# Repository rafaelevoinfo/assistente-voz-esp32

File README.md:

# Assistente de voz "Hi ESP"

Assistente de voz caseiro: você diz **"Hi ESP"** perto de uma placa ESP32-S3, conversa por voz com o **Gemini Live** e, quando o pedido é de programação, ele é **delegado ao Claude Code**. A resposta do Claude Code é falada sozinha quando a tarefa termina, mesmo minutos depois.

```
Mesa                                    VPS (Docker / Dokploy)
┌───────────────────────────┐           ┌────────────────────────────────────────────┐
│ INMP441 ─I2S─► ESP32-S3    │  Wi-Fi    │ servidor (Python + Pipecat)                 │
│   • wake word "Hi ESP"     │◄════════► │   • conversa ◄══► Gemini Live               │
│   • WebSocket              │  WSS      │   • pedidos de código ──► claude -p (fila)  │
│        │ USB serial        │           │   • resultado ──► TTS Gemini ──► placa      │
│        ▼                   │           └────────────────────────────────────────────┘
│ notebook: player.py 🔊     │  (temporário, até ligar um MAX98357A na placa)
└───────────────────────────┘
```

## Projetos

| Pasta | O que é | README |
|---|---|---|
| [`servidor/`](servidor/) | Servidor de voz em Python: ponte com o Gemini Live, fila do Claude Code, TTS. Roda em Docker. | [servidor/README.md](servidor/README.md) |
| [`firmware/AssistenteVoz/`](firmware/AssistenteVoz/) | Firmware da placa ESP32-S3 (Arduino): wake word, WebSocket, envio do mic. | [firmware/AssistenteVoz/README.md](firmware/AssistenteVoz/README.md) |
| [`notebook/`](notebook/) | Player que toca no notebook o áudio que a placa recebe (via USB). | [notebook/README.md](notebook/README.md) |

## Documentação

- [`docs/specs/2026-11-17-assistente-voz-design.md`](docs/specs/2026-11-17-assistente-voz-design.md): o design (o que e por quê).
- [`docs/contrato.md`](docs/contrato.md): **o contrato** de comunicação placa ⇄ servidor ⇄ notebook. Qualquer mudança no protocolo começa aqui.
- [`docs/notas-pipecat.md`](docs/notas-pipecat.md): APIs do Pipecat e do Gemini confirmadas na prática (inclui a pegadinha da API `v1beta`).

## Rodando tudo localmente (desenvolvimento)

O jeito mais fácil: **dê dois cliques em `iniciar.bat`**. Ele sobe o servidor e o player em duas janelas (veja os ajustes no topo do arquivo). Com o servidor rodando na VPS, use `iniciar.bat player` para abrir só o player.

Ou, manualmente, nesta ordem:

1. **Servidor** no notebook: veja [servidor/README.md › Rodar localmente](servidor/README.md#rodar-localmente).
2. **Firmware** com `SERVIDOR_HOST` = IP do notebook, `SERVIDOR_PORTA 8000`, `SERVIDOR_TLS 0`: veja [firmware/AssistenteVoz/README.md](firmware/AssistenteVoz/README.md).
3. **Player** na porta USB da placa: veja [notebook/README.md](notebook/README.md).
4. Diga **"Hi ESP"** e faça uma pergunta.

O `TOKEN_PLACA` do `servidor/.env` e o do `firmware/AssistenteVoz/config.h` precisam ser iguais.

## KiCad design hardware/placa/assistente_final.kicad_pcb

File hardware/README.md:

# Hardware: placa de circuito e caixa

Design: [`docs/superpowers/specs/2026-11-23-placa-e-caixa-design.md`](../docs/superpowers/specs/2026-11-23-placa-e-caixa-design.md).
Tudo aqui é gerado por scripts a partir de **`medidas.json`** (fonte única de medidas, em mm).

## Ferramentas

- **KiCad 10**: desenho da placa (`pcbnew` em Python e `kicad-cli`). Instalado por usuário em
  `%LOCALAPPDATA%\Programs\KiCad\10.0`.
- **Java 25+** (Temurin) e **Freerouting 2.5** (`hardware/ferramentas/freerouting.jar`, fora do git):
  roteamento automático das trilhas.
- **OpenSCAD**: caixa (instalado só na etapa da caixa).

Os scripts da placa e os testes rodam com o Python que vem com o KiCad (com `pip install pytest`):

```
set KPY=%LOCALAPPDATA%\Programs\KiCad\10.0\bin\python.exe
```

## Gerar

```
%KPY% hardware/gerar_medidas_scad.py     # medidas.json -> caixa/medidas.scad
%KPY% hardware/placa/netlist.py          # ligações -> placa/assistente.net
%KPY% hardware/placa/montar_pcb.py       # contorno + componentes -> placa/assistente.kicad_pcb + posicoes.json
%KPY% hardware/placa/rotear.py           # Freerouting + planos de GND -> placa/assistente_final.kicad_pcb
```

## Medidas

Edite `medidas.json` e regenere o que depende dele. Os valores listados em `_a_confirmar`
ainda precisam ser medidos com régua antes de encomendar a placa.

## Testes

```
%KPY% -m pytest hardware/tests -v
```

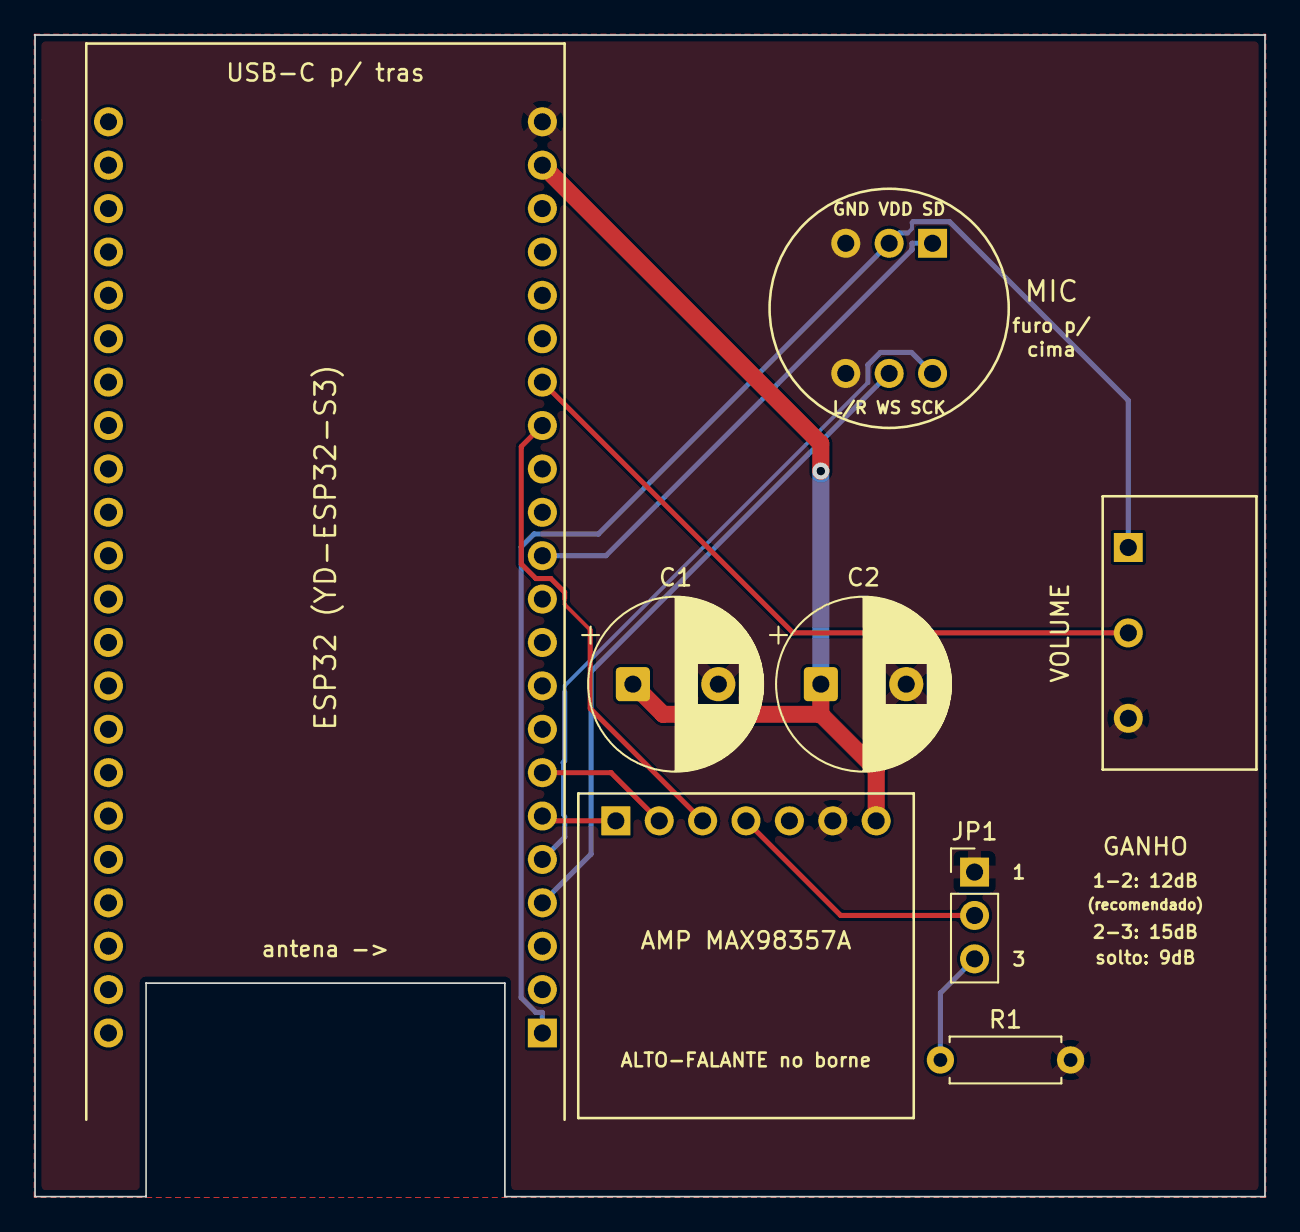
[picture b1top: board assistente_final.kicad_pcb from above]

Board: 2 copper layers, 72.0 x 68.0 mm, 8 parts (0 on the bottom side), 12 nets.

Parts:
C1, C2: 470-1000uF 10V; CP_Radial_D10.0mm_P5.00mm
JP1: GANHO 9/12/15dB; PinHeader_1x03_P2.54mm_Vertical
R1: 100k; R_Axial_DIN0207_L6.3mm_D2.5mm_P7.62mm_Horizontal
RV1: B10K WH148; WH148_Horizontal
U1: YD-ESP32-S3; YD_ESP32_S3_Soquete
U2: INMP441; INMP441_Soquete
U3: MAX98357A; MAX98357A_Soquete

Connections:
/+3V3: RV1.1, U1.1, U2.2
/+5V: C1.1, C2.1, U1.21, U3.7
/AMP_BCLK: U1.7, U3.2
/AMP_DIN: U1.15, U3.3
/AMP_LRC: U1.6, U3.1
/GAIN: JP1.2, U3.4
/GAIN_15DB: JP1.3, R1.1
/GND: C1.2, C2.2, JP1.1, R1.2, RV1.3, U1.22, U2.3, U2.6, U3.6
/I2S_SCK: U1.5, U2.4
/I2S_SD: U1.12, U2.1
/I2S_WS: U1.4, U2.5
/VOL: RV1.2, U1.16

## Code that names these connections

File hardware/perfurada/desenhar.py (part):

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COR = {"+3V3": "#d97706", "+5V": "#dc2626", "GND": "#111827", "I2S_WS": "#2563eb", "I2S_SCK": "#7c3aed",
       "I2S_SD": "#059669", "AMP_LRC": "#0891b2", "AMP_BCLK": "#db2777", "AMP_DIN": "#65a30d",
       "VOL": "#ea580c", "GAIN": "#64748b", "GAIN_15DB": "#a855f7"}
NOME_NET = {"+3V3": "3V3", "+5V": "5V", "GND": "GND", "I2S_WS": "WS (GPIO4)", "I2S_SCK": "SCK (GPIO5)",
            "I2S_SD": "SD (GPIO8)", "AMP_LRC": "LRC (GPIO6)", "AMP_BCLK": "BCLK (GPIO7)",
            "AMP_DIN": "DIN (GPIO9)", "VOL": "volume (GPIO10)", "GAIN": "ganho", "GAIN_15DB": "ganho 15 dB"}
POS = layout.posicoes_para_caixa()
LARG, PROF = POS["placa"]["largura"], POS["placa"]["profundidade"]

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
